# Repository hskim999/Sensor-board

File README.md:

# Sensor-board
RRRREEEEAAAAADDD MMMEEE!!!

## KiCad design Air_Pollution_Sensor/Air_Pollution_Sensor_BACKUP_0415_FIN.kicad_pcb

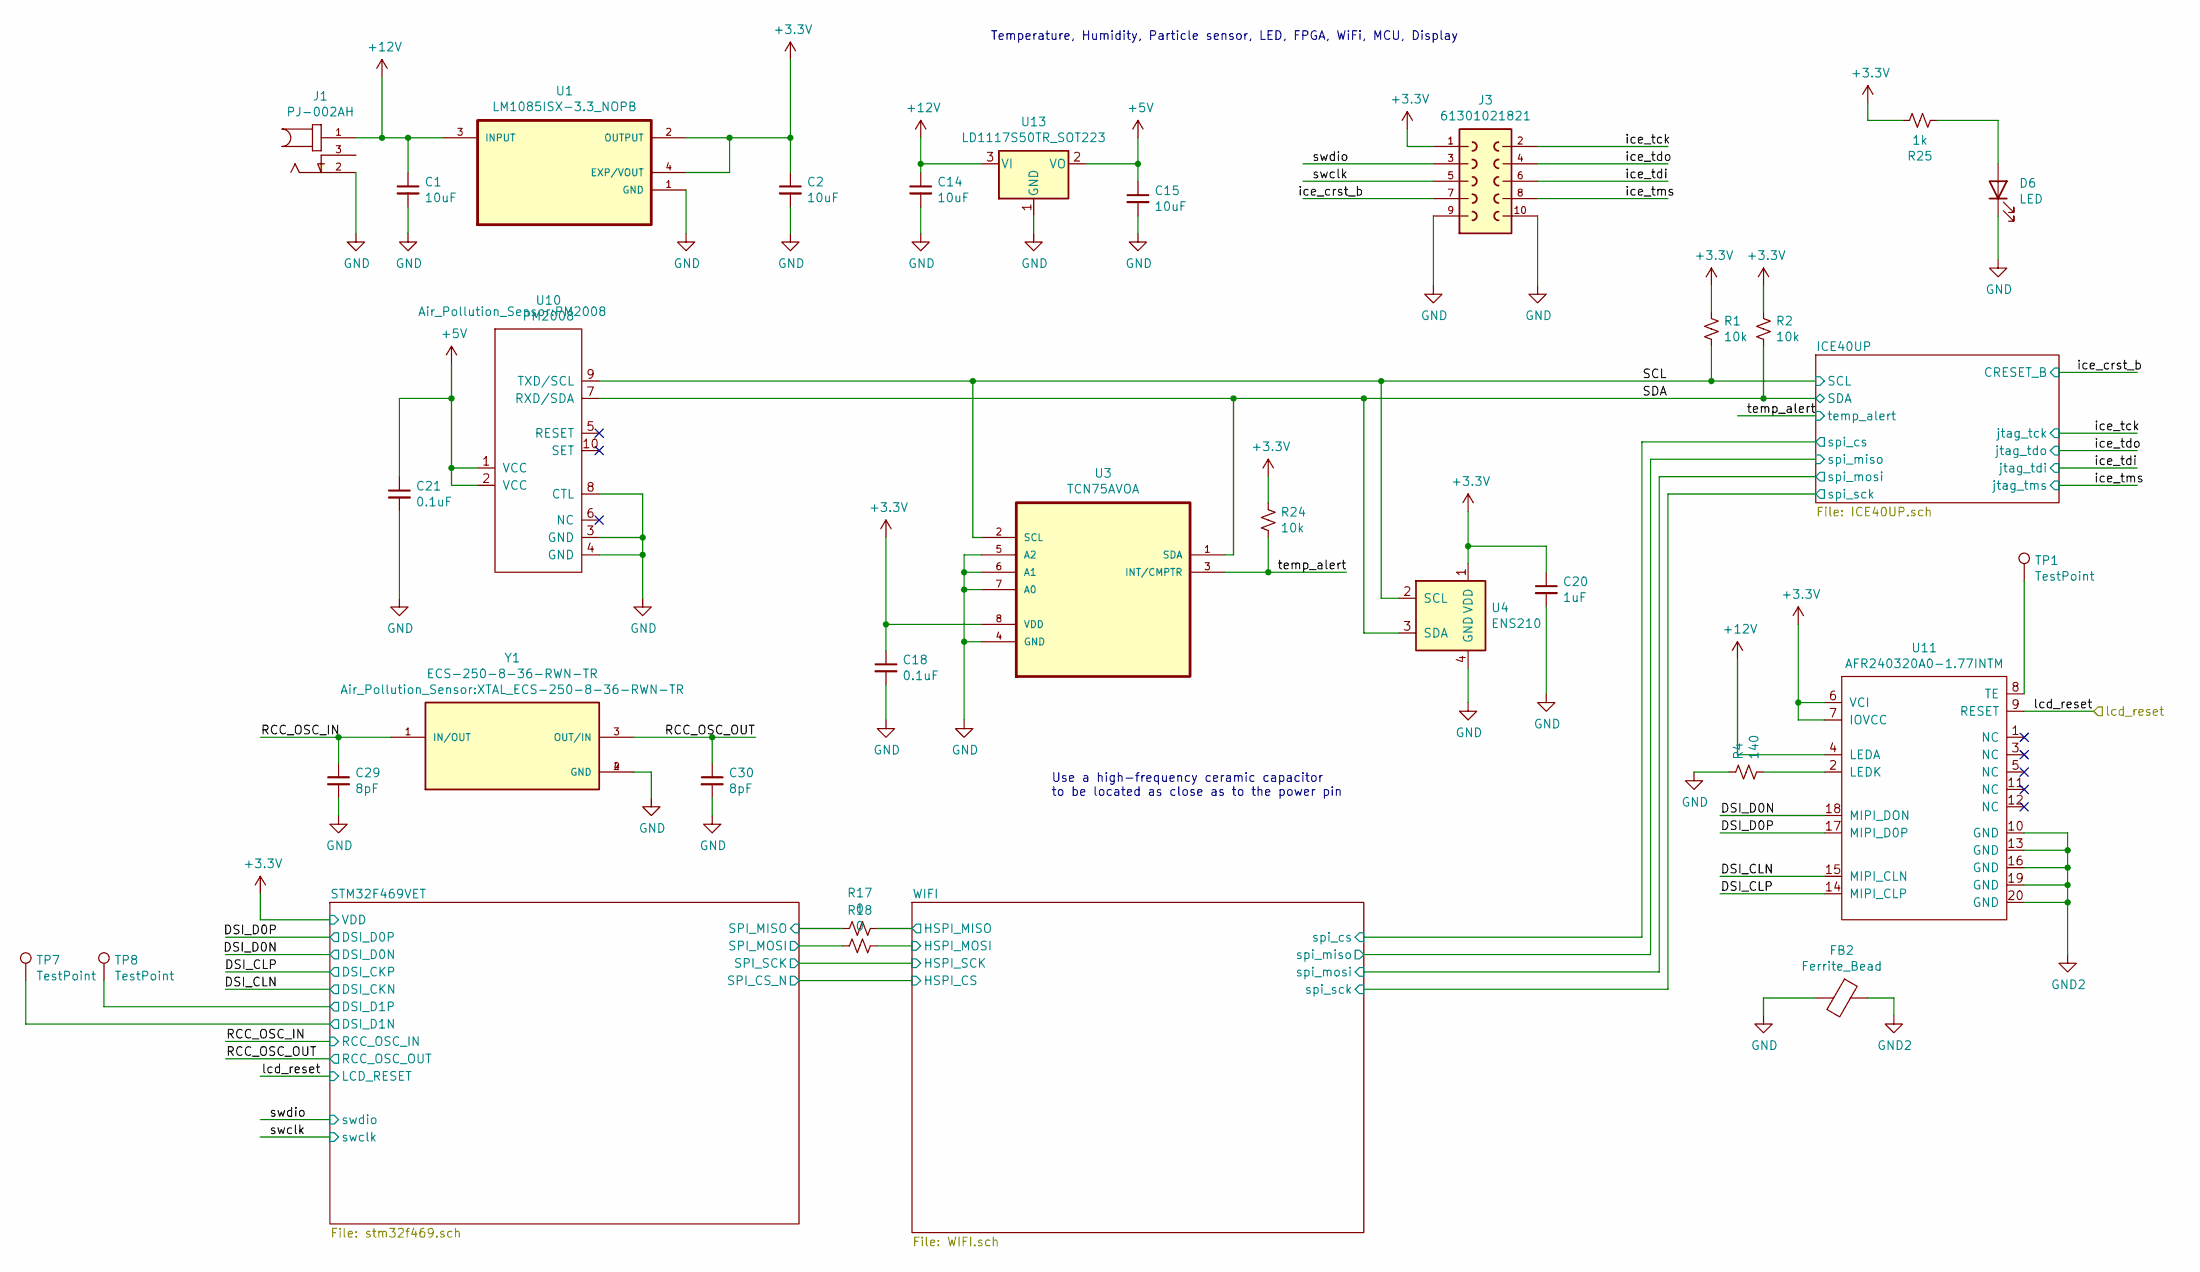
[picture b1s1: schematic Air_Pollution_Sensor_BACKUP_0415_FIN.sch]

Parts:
C1, C2: 10uF; C_1206_3216Metric_Pad1.33x1.80mm_HandSolder
C14, C15: 10uF; C_0805_2012Metric_Pad1.18x1.45mm_HandSolder
C18, C21: 0.1uF; C_0805_2012Metric_Pad1.18x1.45mm_HandSolder
C20: 1uF; C_0805_2012Metric_Pad1.18x1.45mm_HandSolder
C29, C30: 8pF; C_0805_2012Metric_Pad1.18x1.45mm_HandSolder
D6: LED; LED_0805_2012Metric_Pad1.15x1.40mm_HandSolder
FB2: Ferrite_Bead; C_0805_2012Metric_Pad1.18x1.45mm_HandSolder
J1: PJ-002AH; CUI_PJ-002AH
J3: 61301021821
R1, R2, R24: 10k; R_0805_2012Metric_Pad1.20x1.40mm_HandSolder
R4: 140; R_0805_2012Metric_Pad1.20x1.40mm_HandSolder
R17, R18: 0; R_0805_2012Metric_Pad1.20x1.40mm_HandSolder
R25: 1k; R_0805_2012Metric_Pad1.20x1.40mm_HandSolder
TP1, TP7, TP8: TestPoint; TestPoint_THTPad_D2.0mm_Drill1.0mm
U1: LM1085ISX-3.3_NOPB; TO254P1524X483-4N
U3: TCN75AVOA; SOIC127P600X175-8N; MPN TCN75AVOA
U4: ENS210; AMS_QFN-4-1EP_2x2mm_P0.95mm_EP0.7x1.6mm
U10: PM2008
U11: AFR240320A0-1.77INTM; AFR240320A0-1.77INTM-I
U13: LD1117S50TR_SOT223; SOT-223-3_TabPin2
Y1: ECS-250-8-36-RWN-TR; XTAL_ECS-250-8-36-RWN-TR; PARTREV 2017

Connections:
+3V3: C2.1, C18.1, C20.1, J3.1, R1.1, R2.2, R24.2, R25.1, U1.2 (OUTPUT), U1.4 (EXP/VOUT), U3.8 (VDD), U4.1 (VDD), U11.6 (VCI), U11.7 (IOVCC); also elsewhere on the board
+5V: C15.1, C21.1, U10.1 (VCC), U10.2 (VCC), U13.2 (VO); also elsewhere on the board
+12V: C1.1, C14.1, J1.1, U1.3 (INPUT), U11.4 (LEDA), U13.3 (VI)
/DSI_CLN: U11.15 (MIPI_CLN); also elsewhere on the board
/DSI_CLP: U11.14 (MIPI_CLP); also elsewhere on the board
/DSI_D0N: U11.18 (MIPI_DON); also elsewhere on the board
/DSI_D0P: U11.17 (MIPI_D0P); also elsewhere on the board
/RCC_OSC_IN: C29.1, Y1.1 (IN/OUT); also elsewhere on the board
/RCC_OSC_OUT: C30.1, Y1.3 (OUT/IN); also elsewhere on the board
/SCL: R1.2, U3.2 (SCL), U4.2 (SCL), U10.9 (TXD/SCL); also elsewhere on the board
/SDA: R2.1, U3.1 (SDA), U4.3 (SDA), U10.7 (RXD/SDA); also elsewhere on the board
/STM32F469VET/DSI_D1N: TP7.1; also elsewhere on the board
/STM32F469VET/DSI_D1P: TP8.1; also elsewhere on the board
/STM32F469VET/SPI_MISO: R17.1; also elsewhere on the board
/STM32F469VET/SPI_MOSI: R18.1; also elsewhere on the board
/WIFI/HSPI_MISO: R17.2; also elsewhere on the board
/WIFI/HSPI_MOSI: R18.2; also elsewhere on the board
/ice_crst_b: J3.7; also elsewhere on the board
/ice_tck: J3.2; also elsewhere on the board
/ice_tdi: J3.6; also elsewhere on the board
/ice_tdo: J3.4; also elsewhere on the board
/ice_tms: J3.8; also elsewhere on the board
/lcd_reset: U11.9 (RESET); also elsewhere on the board
/swclk: J3.5; also elsewhere on the board
/swdio: J3.3; also elsewhere on the board
/temp_alert: R24.1, U3.3 (INT/CMPTR); also elsewhere on the board
GND: C1.2, C2.2, C14.2, C15.2, C18.2, C20.2, C21.2, C29.2, C30.2, D6.1 (K), FB2.2, J1.2, J3.9, J3.10, R4.2, U1.1 (GND), U3.4 (GND), U3.5 (A2), U3.6 (A1), U3.7 (A0), U4.4 (GND), U4.5 (GND), U10.3 (GND), U10.4 (GND), U10.8 (CTL), U13.1 (GND), Y1.2 (GND), Y1.4 (GND); also elsewhere on the board
GND2: FB2.1, U11.10 (GND), U11.13 (GND), U11.16 (GND), U11.19 (GND), U11.20 (GND)
unnamed: D6.2 (A), R25.2
unnamed: R4.1, U11.2 (LEDK)
unnamed: TP1.1, U11.8 (TE)

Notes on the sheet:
Use a high-frequency ceramic capacitor to be located as close as to the power pin
Temperature, Humidity, Particle sensor, LED, FPGA, WiFi, MCU, Display

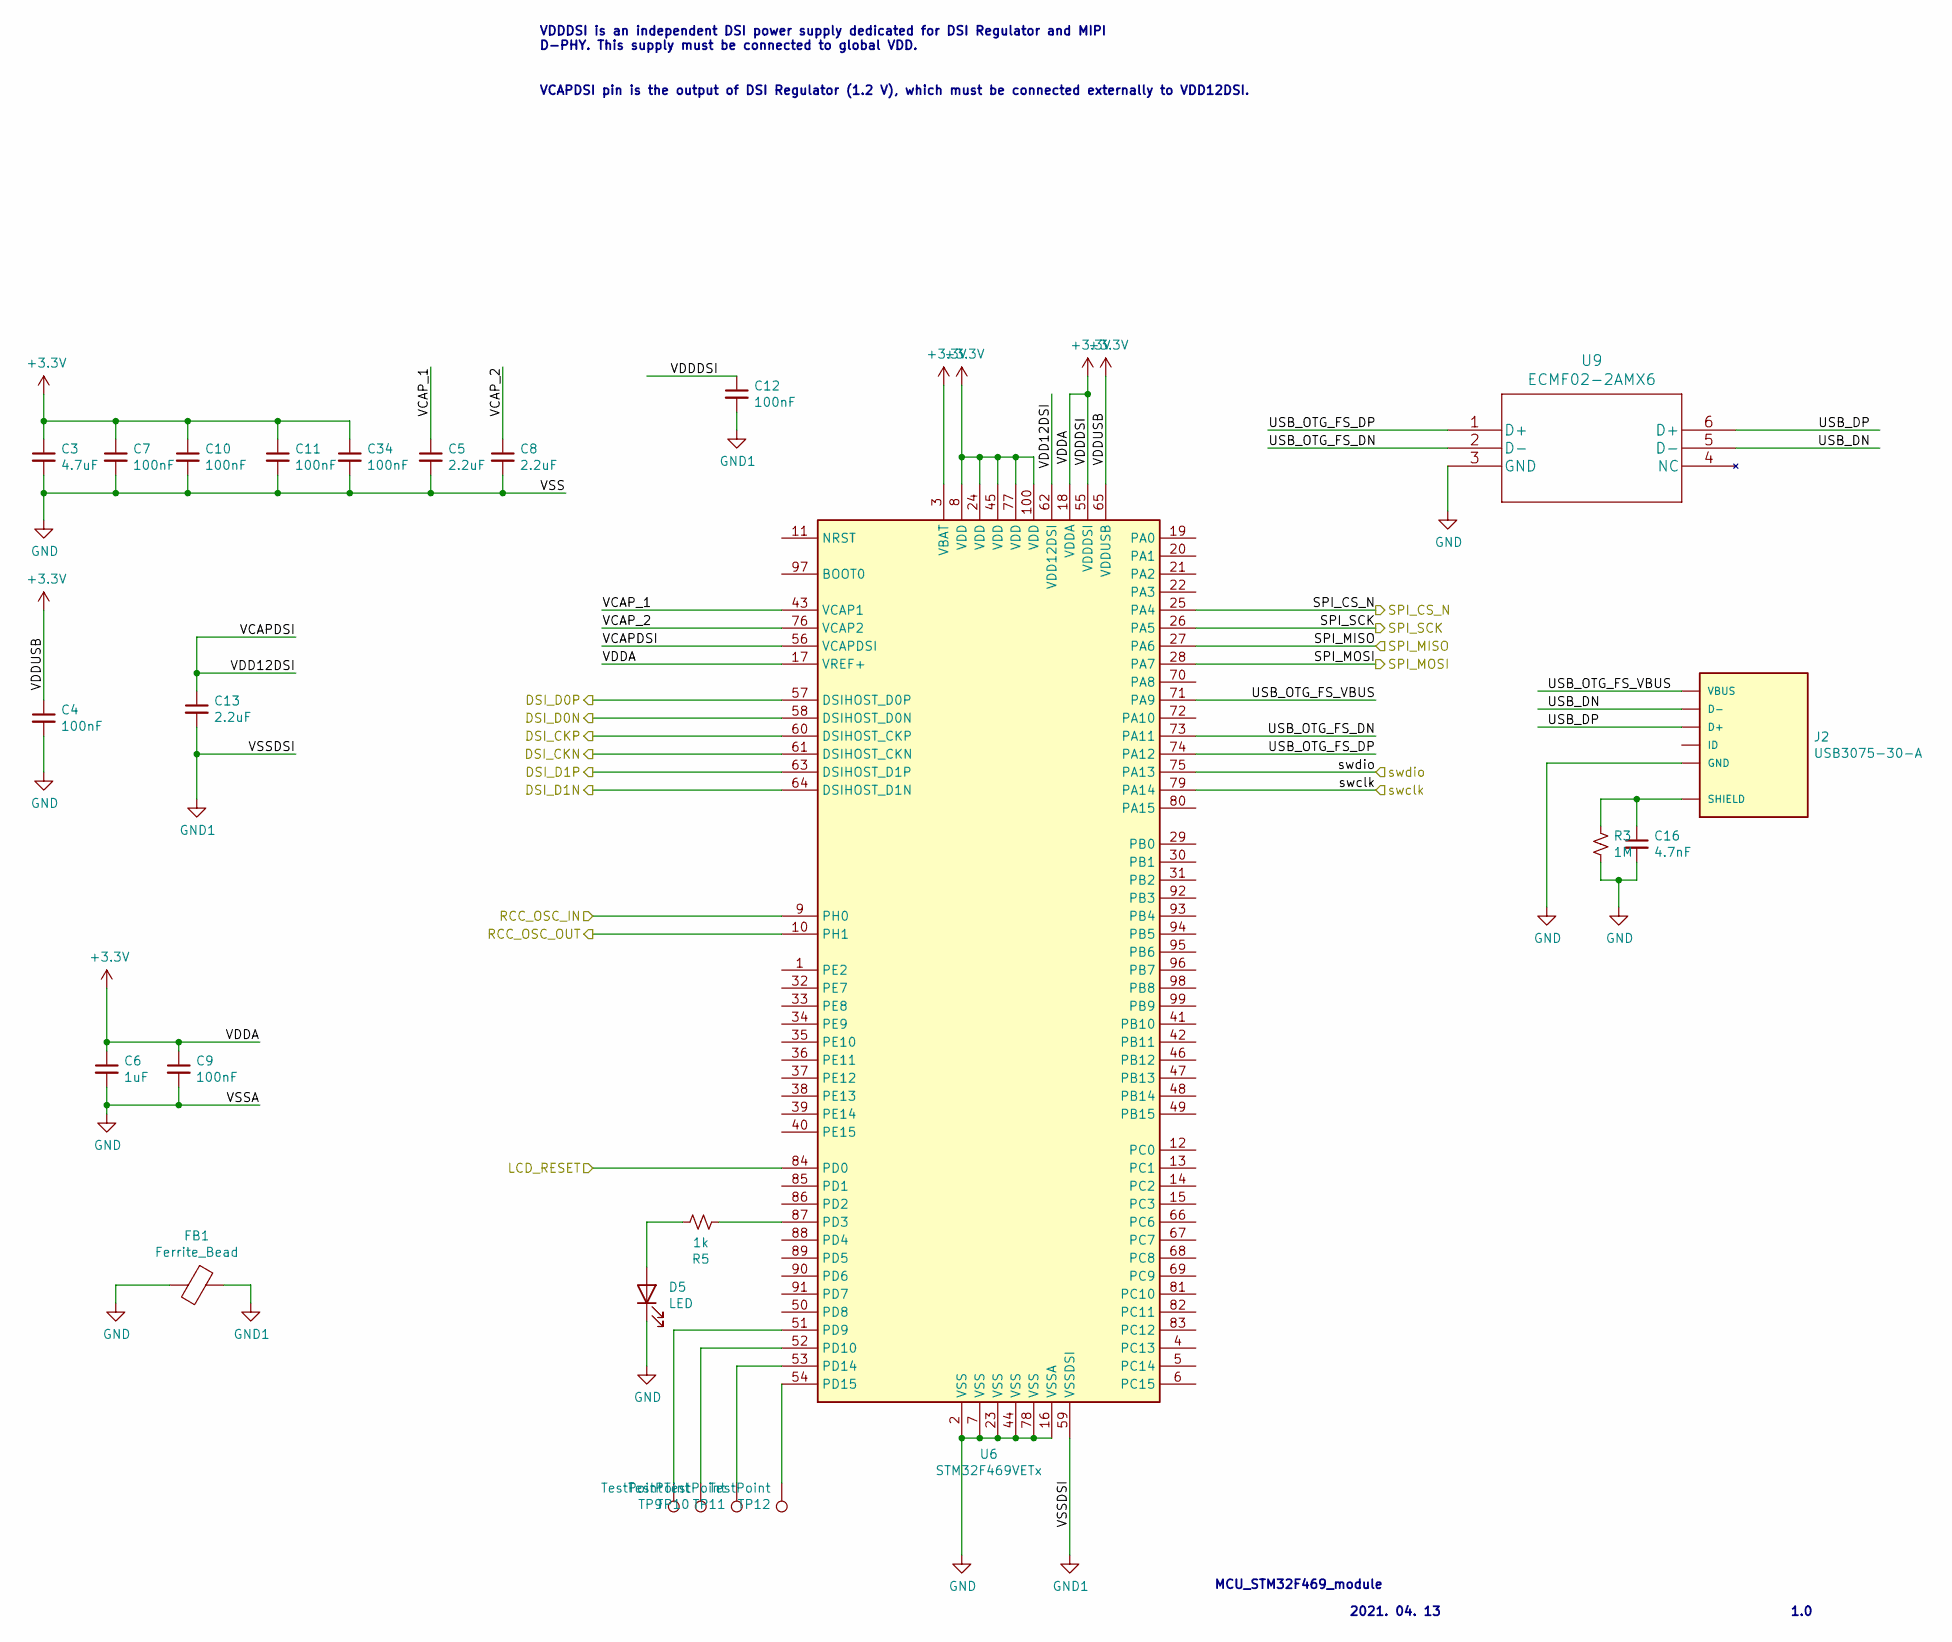
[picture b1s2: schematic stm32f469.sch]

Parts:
C3: 4.7uF; C_0805_2012Metric_Pad1.18x1.45mm_HandSolder
C4, C7, C9, C10, C11, C12, C34: 100nF; C_0805_2012Metric_Pad1.18x1.45mm_HandSolder
C5, C8, C13: 2.2uF; C_0805_2012Metric_Pad1.18x1.45mm_HandSolder
C6: 1uF; C_0805_2012Metric_Pad1.18x1.45mm_HandSolder
C16: 4.7nF; C_0805_2012Metric_Pad1.18x1.45mm_HandSolder
D5: LED; LED_0805_2012Metric_Pad1.15x1.40mm_HandSolder
FB1: Ferrite_Bead; C_0805_2012Metric_Pad1.18x1.45mm_HandSolder
J2: USB3075-30-A; GCT_USB3075-30-A; PARTREV D3
R3: 1M; R_0805_2012Metric_Pad1.20x1.40mm_HandSolder
R5: 1k; R_0805_2012Metric_Pad1.20x1.40mm_HandSolder
TP9, TP10, TP11, TP12: TestPoint; TestPoint_Pad_D2.0mm
U6: STM32F469VETx; LQFP-100_14x14mm_P0.5mm
U9: ECMF02-2AMX6

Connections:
+3V3: C3.1, C4.1, C6.1, C7.1, C9.1, C10.1, C11.1, C12.1, C34.1, U6.3 (VBAT), U6.8 (VDD), U6.17 (VREF+), U6.18 (VDDA), U6.24 (VDD), U6.45 (VDD), U6.55 (VDDDSI), U6.65 (VDDUSB), U6.77 (VDD), U6.100 (VDD); also elsewhere on the board
/DSI_CLN: U6.61 (DSIHOST_CKN); also elsewhere on the board
/DSI_CLP: U6.60 (DSIHOST_CKP); also elsewhere on the board
/DSI_D0N: U6.58 (DSIHOST_D0N); also elsewhere on the board
/DSI_D0P: U6.57 (DSIHOST_D0P); also elsewhere on the board
/RCC_OSC_IN: U6.9 (PH0); also elsewhere on the board
/RCC_OSC_OUT: U6.10 (PH1); also elsewhere on the board
/STM32F469VET/DSI_D1N: U6.64 (DSIHOST_D1N); also elsewhere on the board
/STM32F469VET/DSI_D1P: U6.63 (DSIHOST_D1P); also elsewhere on the board
/STM32F469VET/SPI_MISO: U6.27 (PA6); also elsewhere on the board
/STM32F469VET/SPI_MOSI: U6.28 (PA7); also elsewhere on the board
/STM32F469VET/USB_DN: J2.2 (D-), U9.5 (D-)
/STM32F469VET/USB_DP: J2.3 (D+), U9.6 (D+)
/STM32F469VET/USB_OTG_FS_DN: U6.73 (PA11), U9.2 (D-)
/STM32F469VET/USB_OTG_FS_DP: U6.74 (PA12), U9.1 (D+)
/STM32F469VET/USB_OTG_FS_VBUS: J2.1 (VBUS), U6.71 (PA9)
/STM32F469VET/VCAPDSI: C13.1, U6.56 (VCAPDSI), U6.62 (VDD12DSI)
/STM32F469VET/VCAP_1: C5.1, U6.43 (VCAP1)
/STM32F469VET/VCAP_2: C8.1, U6.76 (VCAP2)
/WIFI/HSPI_CS: U6.25 (PA4); also elsewhere on the board
/WIFI/HSPI_SCK: U6.26 (PA5); also elsewhere on the board
/lcd_reset: U6.84 (PD0); also elsewhere on the board
/swclk: U6.79 (PA14); also elsewhere on the board
/swdio: U6.75 (PA13); also elsewhere on the board
GND: C3.2, C4.2, C5.2, C6.2, C7.2, C8.2, C9.2, C10.2, C11.2, C16.2, C34.2, D5.1 (K), FB1.2, J2.5 (GND), R3.2, U6.2 (VSS), U6.7 (VSS), U6.16 (VSSA), U6.23 (VSS), U6.44 (VSS), U6.78 (VSS), U9.3 (GND); also elsewhere on the board
GND1: C12.2, C13.2, FB1.1, U6.59 (VSSDSI)
unnamed: C16.1, J2.S1 (SHIELD), J2.S2 (SHIELD), J2.S3 (SHIELD), J2.S4 (SHIELD), J2.S5 (SHIELD), J2.S6 (SHIELD), R3.1
unnamed: D5.2 (A), R5.1
unnamed: R5.2, U6.87 (PD3)
unnamed: TP9.1, U6.51 (PD9)
unnamed: TP10.1, U6.52 (PD10)
unnamed: TP11.1, U6.53 (PD14)
unnamed: TP12.1, U6.54 (PD15)

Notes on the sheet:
VCAPDSI pin is the output of DSI Regulator (1.2 V), which must be connected externally to VDD12DSI.
VDDDSI is an independent DSI power supply dedicated for DSI Regulator and MIPI D-PHY. This supply must be connected to global VDD.
MCU_STM32F469_module
1.0
2021. 04. 13

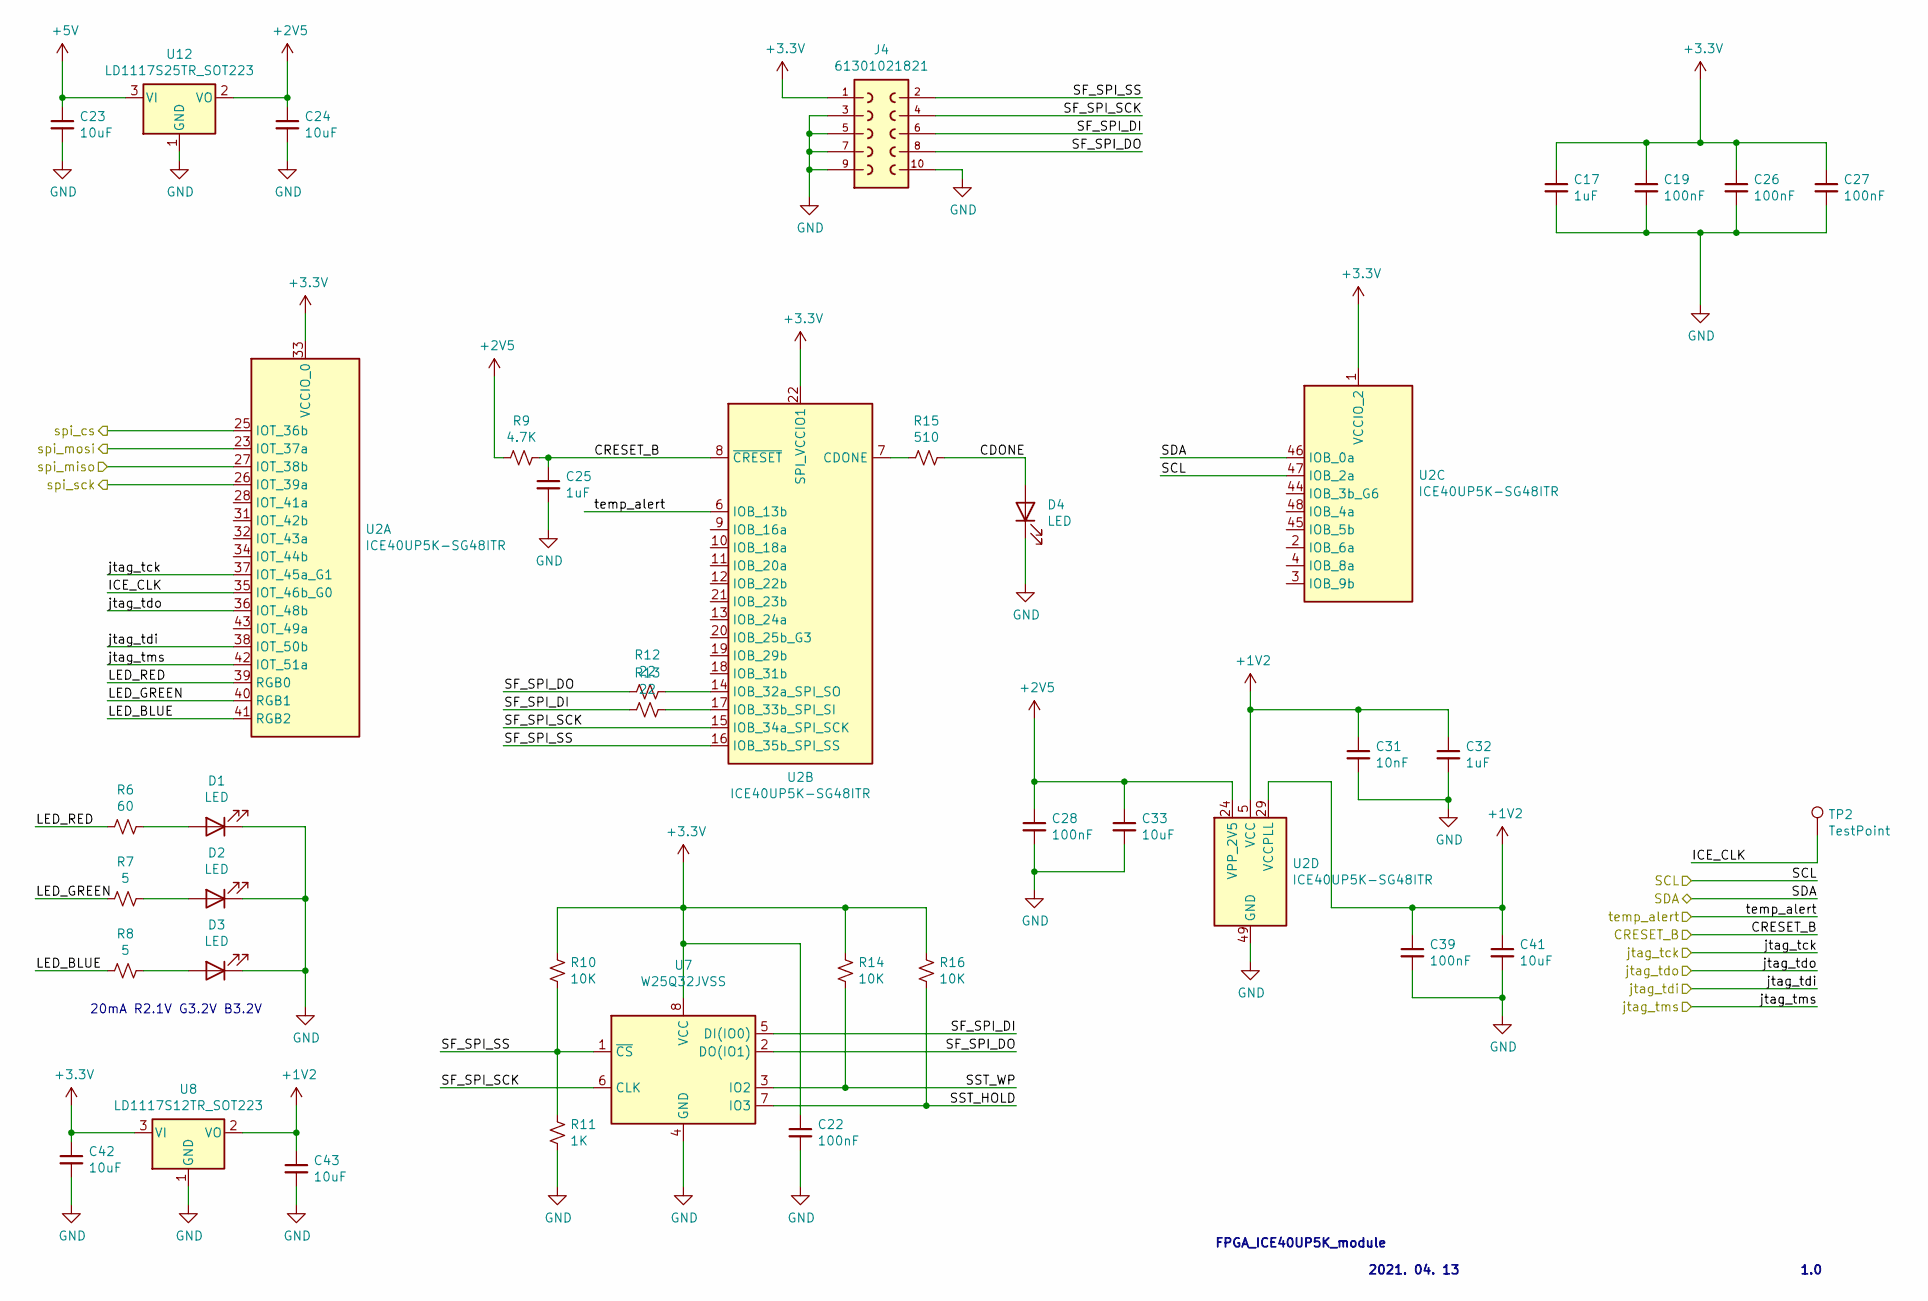
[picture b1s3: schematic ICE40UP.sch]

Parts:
C17, C25, C32: 1uF; C_0805_2012Metric_Pad1.18x1.45mm_HandSolder
C19, C22, C26, C27, C28, C39: 100nF; C_0805_2012Metric_Pad1.18x1.45mm_HandSolder
C23, C24, C33, C41, C42, C43: 10uF; C_0805_2012Metric_Pad1.18x1.45mm_HandSolder
C31: 10nF; C_0805_2012Metric_Pad1.18x1.45mm_HandSolder
D1, D2, D3: LED; C503B-GAN-CB0F0791
D4: LED; LED_0805_2012Metric_Pad1.15x1.40mm_HandSolder
J4: 61301021821
R6: 60; R_0805_2012Metric_Pad1.20x1.40mm_HandSolder
R7, R8: 5; R_0805_2012Metric_Pad1.20x1.40mm_HandSolder
R9: 4.7K; R_0805_2012Metric_Pad1.20x1.40mm_HandSolder
R10, R14, R16: 10K; R_0805_2012Metric_Pad1.20x1.40mm_HandSolder
R11: 1K; R_0805_2012Metric_Pad1.20x1.40mm_HandSolder
R12, R13: 22; R_0805_2012Metric_Pad1.20x1.40mm_HandSolder
R15: 510; R_0805_2012Metric_Pad1.20x1.40mm_HandSolder
TP2: TestPoint; TestPoint_THTPad_D2.0mm_Drill1.0mm
U2: ICE40UP5K-SG48ITR; QFN-48-1EP_7x7mm_P0.5mm_EP5.6x5.6mm
U7: W25Q32JVSS; SOIC-8_5.23x5.23mm_P1.27mm
U8: LD1117S12TR_SOT223; SOT-223-3_TabPin2
U12: LD1117S25TR_SOT223; SOT-223-3_TabPin2

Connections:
+1V2: C31.1, C32.1, C39.1, C41.1, C43.1, U2.5 (VCC), U2.29 (VCCPLL), U2.30 (VCC), U8.2 (VO)
+2V5: C24.1, C28.1, C33.1, R9.2, U2.24 (VPP_2V5), U12.2 (VO)
+3V3: C17.1, C19.1, C22.1, C26.1, C27.1, C42.1, J4.1, R10.1, R14.1, R16.1, U2.1 (VCCIO_2), U2.22 (SPI_VCCIO1), U2.33 (VCCIO_0), U7.8 (VCC), U8.3 (VI); also elsewhere on the board
+5V: C23.1, U12.3 (VI); also elsewhere on the board
/ICE40UP/CDONE: D4.2 (A), R15.1
/ICE40UP/ICE_CLK: TP2.1, U2.35 (IOT_46b_G0)
/ICE40UP/LED_BLUE: R8.2, U2.41 (RGB2)
/ICE40UP/LED_GREEN: R7.2, U2.40 (RGB1)
/ICE40UP/LED_RED: R6.2, U2.39 (RGB0)
/ICE40UP/SF_SPI_DI: J4.6, R13.2, U7.5 (DI(IO0))
/ICE40UP/SF_SPI_DO: J4.8, R12.2, U7.2 (DO(IO1))
/ICE40UP/SF_SPI_SCK: J4.4, U2.15 (IOB_34a_SPI_SCK), U7.6 (CLK)
/ICE40UP/SF_SPI_SS: J4.2, R10.2, R11.1, U2.16 (IOB_35b_SPI_SS), U7.1 (~CS)
/ICE40UP/SST_HOLD: R16.2, U7.7 (IO3)
/ICE40UP/SST_WP: R14.2, U7.3 (IO2)
/ICE40UP/spi_cs: U2.25 (IOT_36b); also elsewhere on the board
/ICE40UP/spi_miso: U2.27 (IOT_38b); also elsewhere on the board
/ICE40UP/spi_mosi: U2.23 (IOT_37a); also elsewhere on the board
/ICE40UP/spi_sck: U2.26 (IOT_39a); also elsewhere on the board
/SCL: U2.47 (IOB_2a); also elsewhere on the board
/SDA: U2.46 (IOB_0a); also elsewhere on the board
/ice_crst_b: C25.1, R9.1, U2.8 (~CRESET); also elsewhere on the board
/ice_tck: U2.37 (IOT_45a_G1); also elsewhere on the board
/ice_tdi: U2.38 (IOT_50b); also elsewhere on the board
/ice_tdo: U2.36 (IOT_48b); also elsewhere on the board
/ice_tms: U2.42 (IOT_51a); also elsewhere on the board
/temp_alert: U2.6 (IOB_13b); also elsewhere on the board
GND: C17.2, C19.2, C22.2, C23.2, C24.2, C25.2, C26.2, C27.2, C28.2, C31.2, C32.2, C33.2, C39.2, C41.2, C42.2, C43.2, D1.1 (K), D2.1 (K), D3.1 (K), D4.1 (K), J4.3, J4.5, J4.7, J4.9, J4.10, R11.2, U2.49 (GND), U7.4 (GND), U8.1 (GND), U12.1 (GND); also elsewhere on the board
unnamed: D1.2 (A), R6.1
unnamed: D2.2 (A), R7.1
unnamed: D3.2 (A), R8.1
unnamed: R12.1, U2.14 (IOB_32a_SPI_SO)
unnamed: R13.1, U2.17 (IOB_33b_SPI_SI)
unnamed: R15.2, U2.7 (CDONE)

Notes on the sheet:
20mA R2.1V G3.2V B3.2V
FPGA_ICE40UP5K_module
2021. 04. 13
1.0

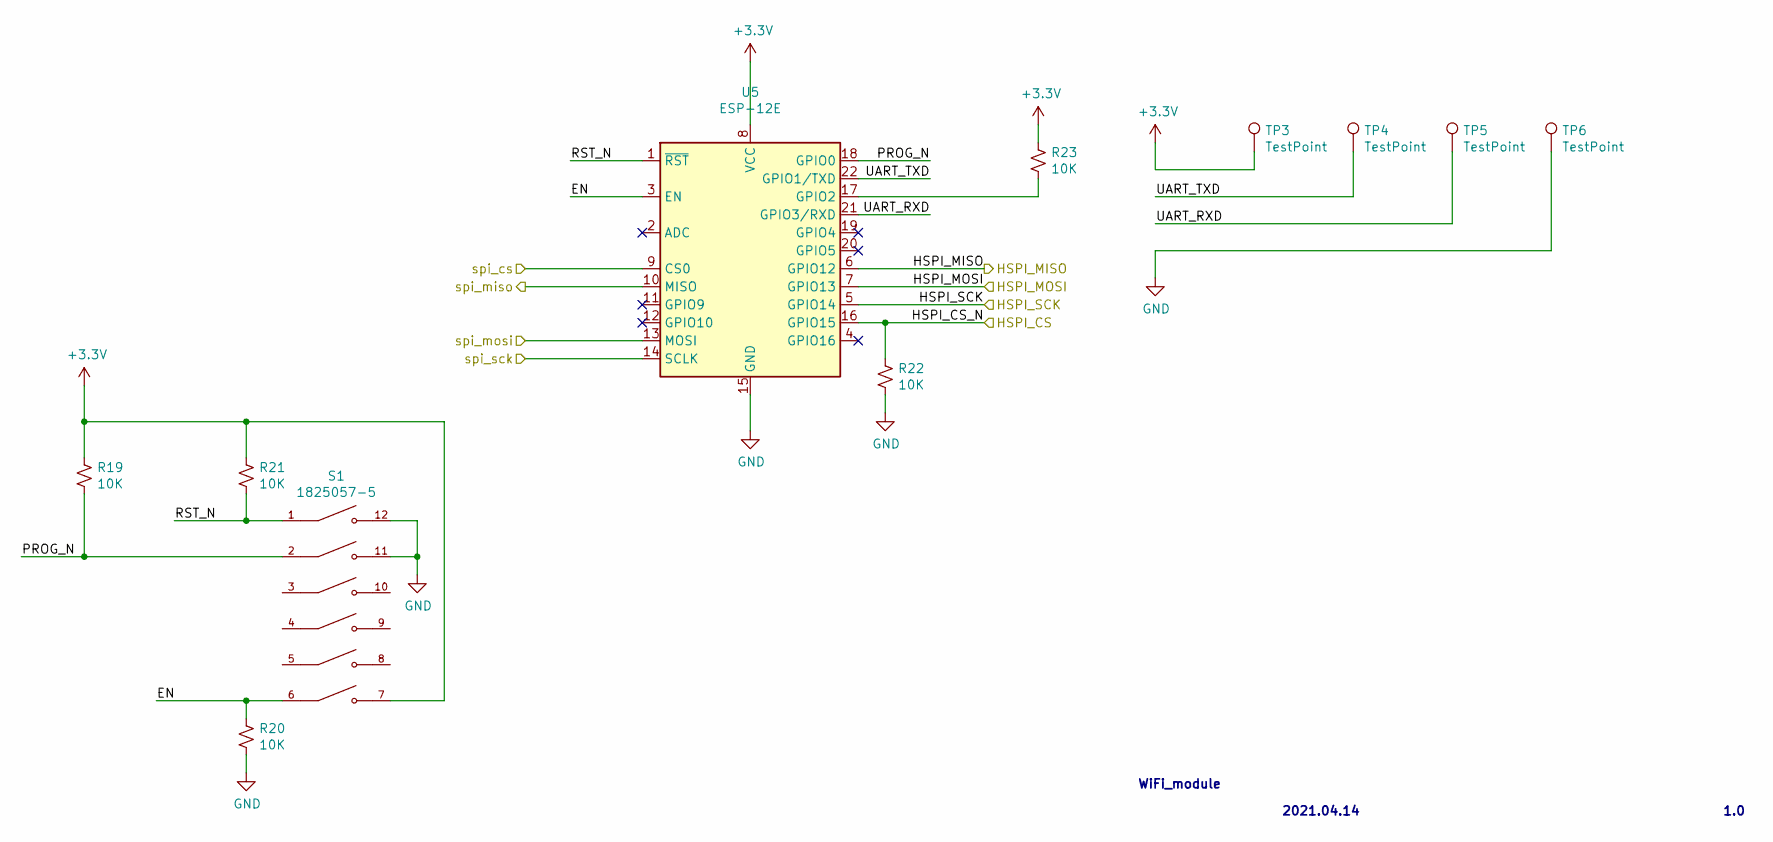
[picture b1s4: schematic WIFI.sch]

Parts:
R19, R20, R21, R22, R23: 10K; R_0805_2012Metric_Pad1.20x1.40mm_HandSolder
S1: 1825057-5; DIP762W56P254L1772H585Q12
TP3, TP4, TP5, TP6: TestPoint; TestPoint_THTPad_D2.0mm_Drill1.0mm
U5: ESP-12E

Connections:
+3V3: R19.1, R21.1, R23.1, S1.7, TP3.1, U5.8 (VCC); also elsewhere on the board
/ICE40UP/spi_cs: U5.9 (CS0); also elsewhere on the board
/ICE40UP/spi_miso: U5.10 (MISO); also elsewhere on the board
/ICE40UP/spi_mosi: U5.13 (MOSI); also elsewhere on the board
/ICE40UP/spi_sck: U5.14 (SCLK); also elsewhere on the board
/WIFI/EN: R20.1, S1.6, U5.3 (EN)
/WIFI/HSPI_CS: R22.1, U5.16 (GPIO15); also elsewhere on the board
/WIFI/HSPI_MISO: U5.6 (GPIO12); also elsewhere on the board
/WIFI/HSPI_MOSI: U5.7 (GPIO13); also elsewhere on the board
/WIFI/HSPI_SCK: U5.5 (GPIO14); also elsewhere on the board
/WIFI/PROG_N: R19.2, S1.2, U5.18 (GPIO0)
/WIFI/RST_N: R21.2, S1.1, U5.1 (~RST)
/WIFI/UART_RXD: TP5.1, U5.21 (GPIO3/RXD)
/WIFI/UART_TXD: TP4.1, U5.22 (GPIO1/TXD)
GND: R20.2, R22.2, S1.11, S1.12, TP6.1, U5.15 (GND); also elsewhere on the board
unnamed: R23.2, U5.17 (GPIO2)

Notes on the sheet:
WiFi_module
1.0
2021.04.14

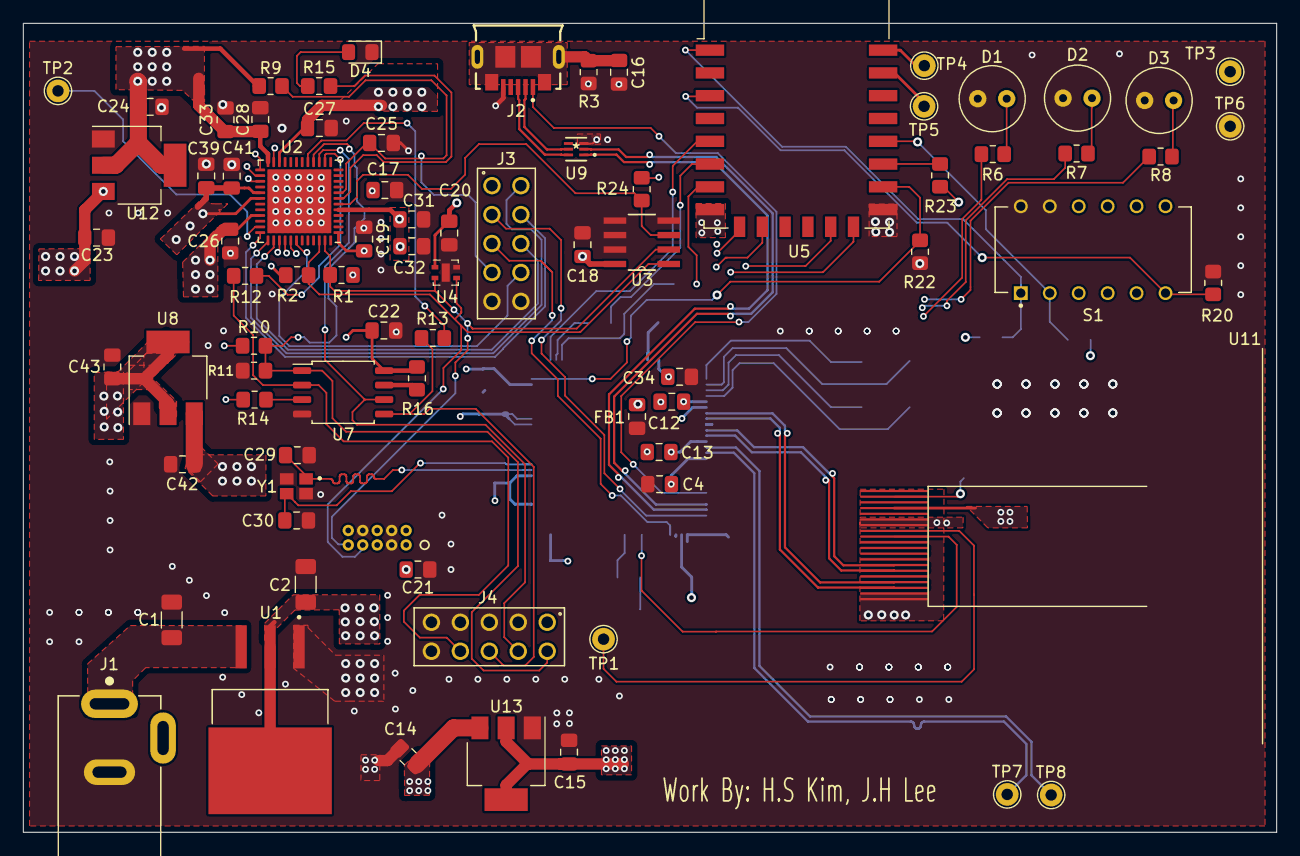
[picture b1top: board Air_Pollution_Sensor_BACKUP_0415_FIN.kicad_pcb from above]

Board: 4 copper layers, 110.0 x 71.0 mm, 100 parts (0 on the bottom side), 77 nets.

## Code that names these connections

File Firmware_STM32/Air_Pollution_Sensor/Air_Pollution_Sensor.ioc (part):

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Mcu.Name=STM32F469V(E-G)Tx
Mcu.Package=LQFP100
Mcu.UserName=STM32F469VETx
PA11.Mode=Device_Only
PA11.Signal=USB_OTG_FS_DM
PA12.Mode=Device_Only
PA12.Signal=USB_OTG_FS_DP
PA13.Mode=Serial_Wire
PA13.Signal=SYS_JTMS-SWDIO
PA14.Mode=Serial_Wire
PA14.Signal=SYS_JTCK-SWCLK
PA15.Mode=NSS_Signal_Hard_Output
PA15.Signal=SPI3_NSS
PA4.Mode=NSS_Signal_Hard_Output
PA4.Signal=SPI1_NSS
PA5.Mode=Full_Duplex_Master
PA5.Signal=SPI1_SCK
PA6.Mode=Full_Duplex_Master
PA6.Signal=SPI1_MISO
PA7.Mode=Full_Duplex_Master
PA7.Signal=SPI1_MOSI
PA9.Mode=Activate_VBUS
PA9.Signal=USB_OTG_FS_VBUS
PC10.Mode=Full_Duplex_Master
PC10.Signal=SPI3_SCK
PC11.Mode=Full_Duplex_Master
PC11.Signal=SPI3_MISO
PC12.Mode=Full_Duplex_Master
PC12.Signal=SPI3_MOSI
PH0/OSC_IN.Mode=HSE-External-Oscillator
PH0/OSC_IN.Signal=RCC_OSC_IN
PH1/OSC_OUT.Mode=HSE-External-Oscillator
PH1/OSC_OUT.Signal=RCC_OSC_OUT
RCC.HSE_VALUE=25000000
RCC.SYSCLKFreq_VALUE=120000000
RCC.SYSCLKSource=RCC_SYSCLKSOURCE_PLLCLK
board=custom

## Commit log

2021-04-28 Base Commit - PCB Done, Working on STM32
